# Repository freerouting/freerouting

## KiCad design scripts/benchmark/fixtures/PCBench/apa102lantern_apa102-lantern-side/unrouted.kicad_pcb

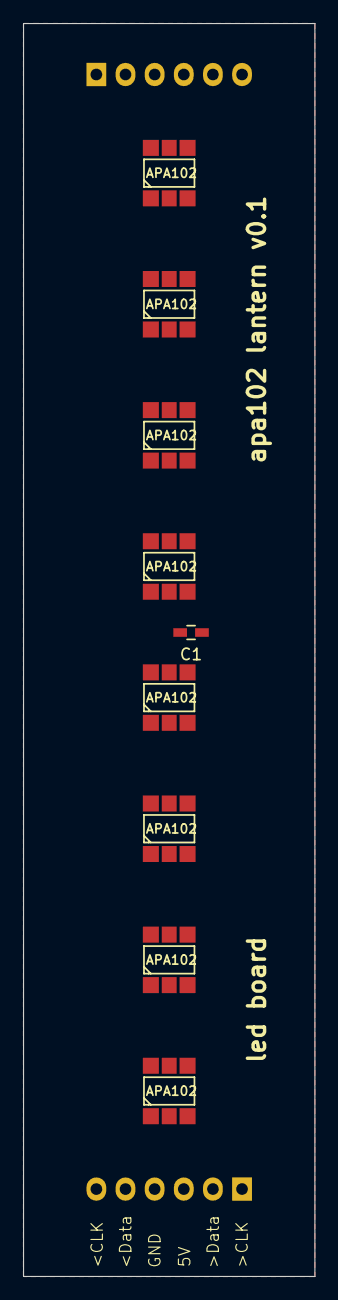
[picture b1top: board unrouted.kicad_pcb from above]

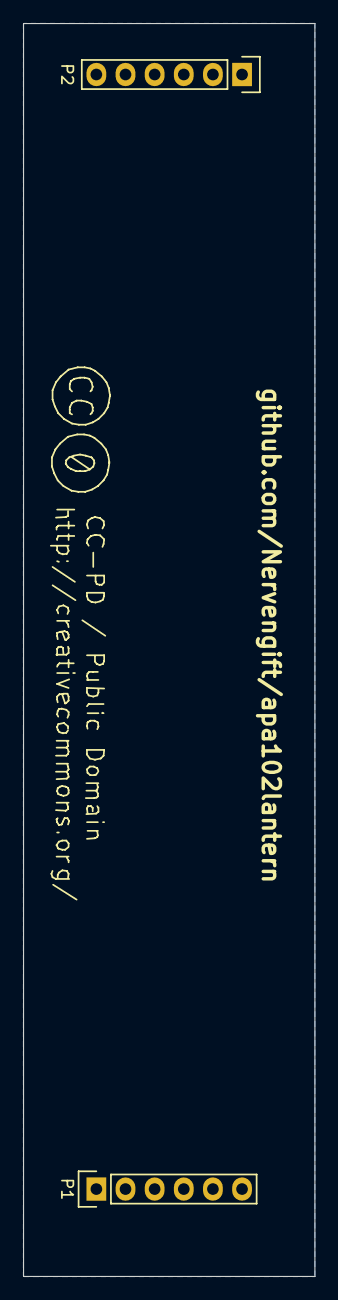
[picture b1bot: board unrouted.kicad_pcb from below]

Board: 2 copper layers, 25.4 x 109.2 mm, 11 parts (2 on the bottom side), 20 nets, no tracks yet.

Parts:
C1: 0.1u; C_0603_HandSoldering
P1, P2: CONN_01X06; Pin_Header_Straight_1x06
U1, U2, U3, U4, U5, U6, U7, U8: APA102

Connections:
/5V: C1.1, P1.3, P2.3, U1.4, U2.4, U3.4, U4.4, U5.4, U6.4, U7.4, U8.4
/>D: P1.2, U1.1
/>clk: P1.1, U1.2
/D>: P1.5, U8.6
/GND: C1.2, P1.4, P2.1, P2.2, P2.4, P2.5, P2.6, U1.3, U2.3, U3.3, U4.3, U5.3, U6.3, U7.3, U8.3
/clk>: P1.6, U8.5
unnamed: U1.5, U2.2
unnamed: U1.6, U2.1
unnamed: U2.5, U3.2
unnamed: U2.6, U3.1
unnamed: U3.5, U4.2
unnamed: U3.6, U4.1
unnamed: U4.5, U5.2
unnamed: U4.6, U5.1
unnamed: U5.5, U6.2
unnamed: U5.6, U6.1
unnamed: U6.5, U7.2
unnamed: U6.6, U7.1
unnamed: U7.5, U8.2
unnamed: U7.6, U8.1

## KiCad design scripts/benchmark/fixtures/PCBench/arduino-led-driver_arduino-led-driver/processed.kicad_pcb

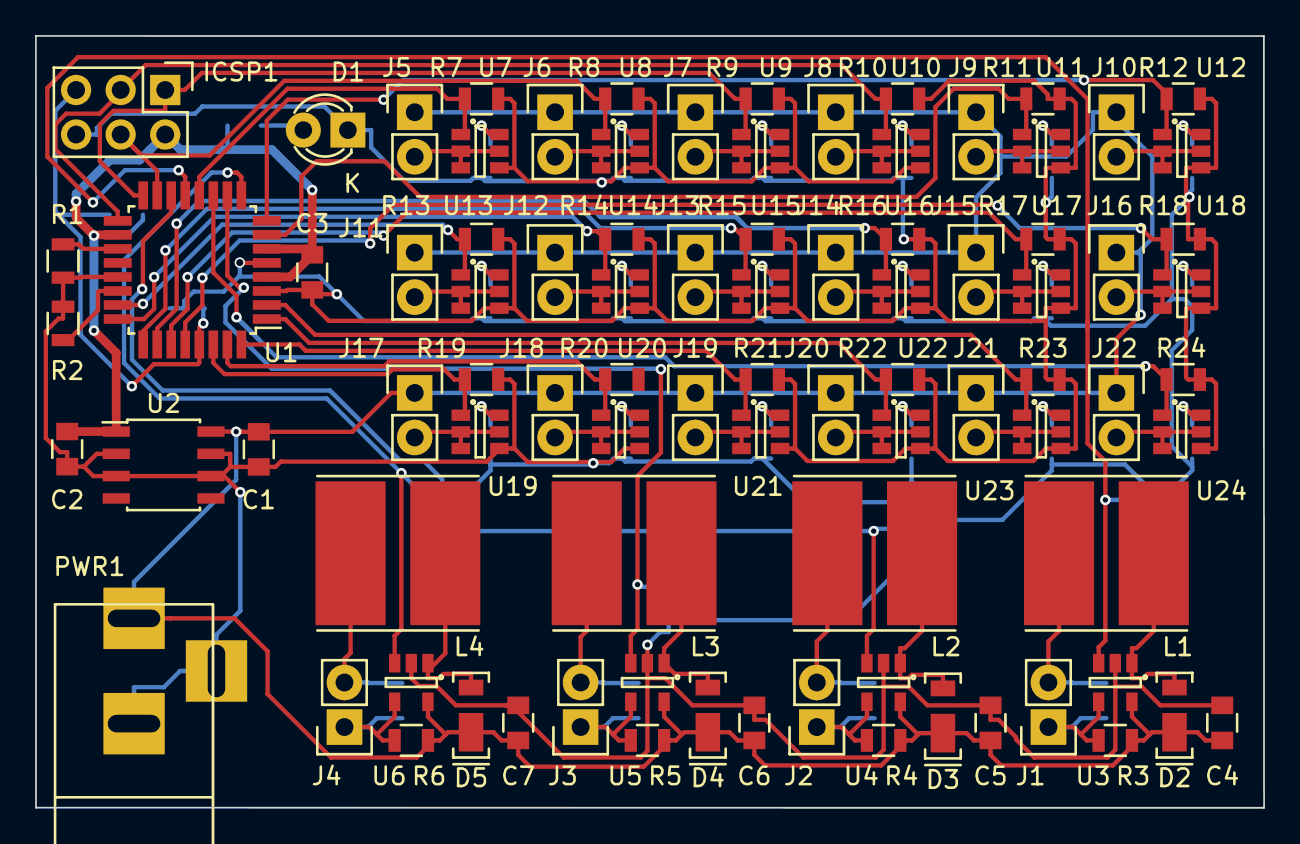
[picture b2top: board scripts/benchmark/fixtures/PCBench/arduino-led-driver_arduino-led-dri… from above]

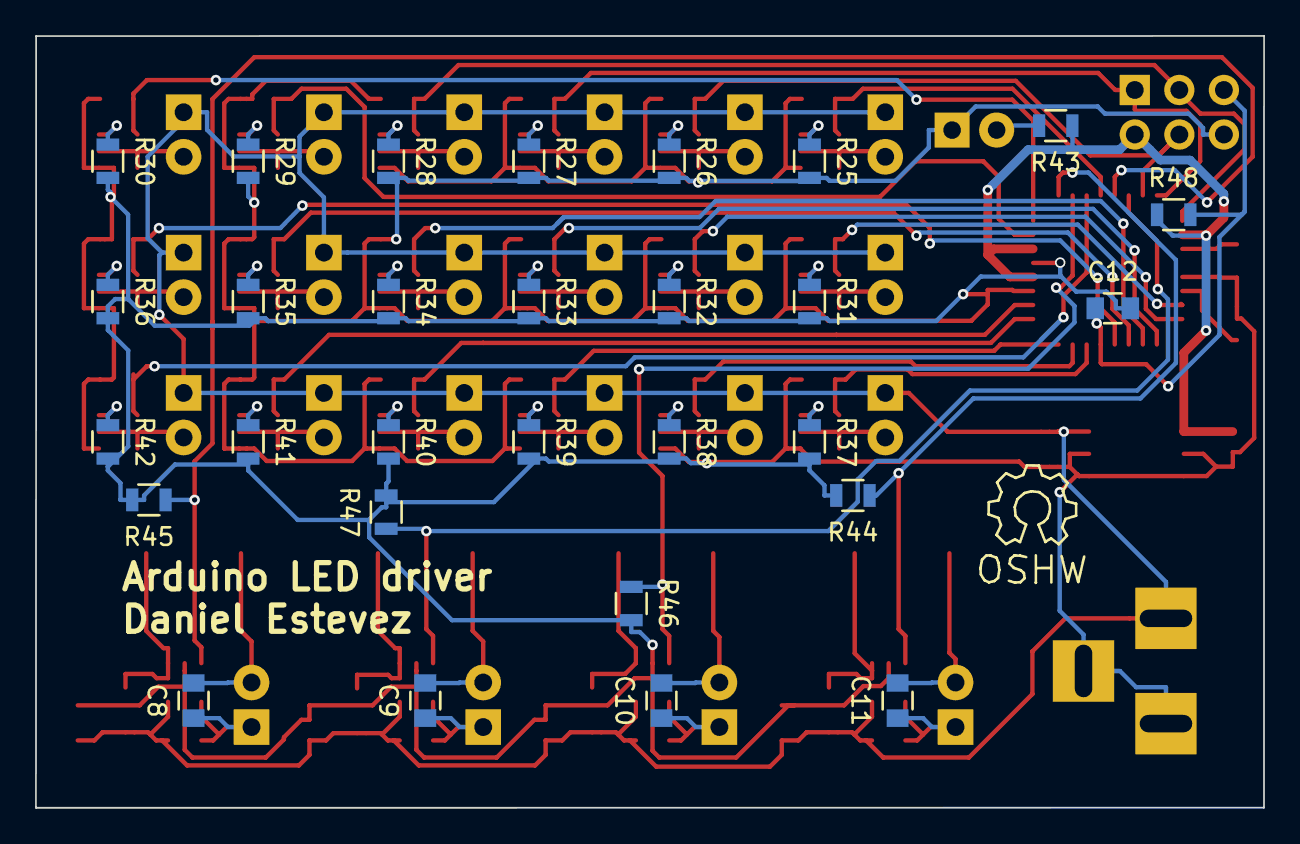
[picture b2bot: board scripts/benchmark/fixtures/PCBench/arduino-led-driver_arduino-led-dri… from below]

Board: 2 copper layers, 70.0 x 44.0 mm, 118 parts (30 on the bottom side), 77 nets.

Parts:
C1: 330n; C_0805
C2, C3, C12: 100n; C_0805
C4, C5, C6, C7: 2.2u; C_0805
C8, C9, C10, C11: 1u; C_0805
D1: LED; LED-3MM
D2, D3, D4, D5: DFLS240L; POWERDI-123
ICSP1: AVR-ISP-6; Pin_Header_Straight_2x03
J1, J2, J3, J4, J5, J6, J7, J8, J9, J10, J11, J12, J13, J14, J15, J16, J17, J18, J19, J20, J21, J22: CONN_01X02; Socket_Strip_Straight_1x02
L1, L2, L3, L4: 33u; VLP8040
Noname_1: Symbol_OSHW-Logo_SilkScreen
PWR1: BARREL_JACK
R1, R2, R7, R8, R9, R10, R11, R12, R13, R14, R15, R16, R17, R18, R19, R20, R21, R22, R23, R24, R25, R26, R27, R28, R29, R30, R31, R32, R33, R34, R35, R36, R37, R38, R39, R40, R41, R42: 100K; R_0805
R3, R4, R5, R6: 130m; R_0805
R43: 10K; R_0805
R44, R45, R46, R47: 2.2K; R_0805
R48: 10k; R_0805
U1: ATMEGA328P-A; TQFP-32_7x7mm_Pitch0.8mm
U2: L78L05ACD; SOIC-8_3.9x4.9mm_Pitch1.27mm
U3, U4, U5, U6: AL8808; SOT-23-5
U7, U8, U9, U10, U11, U12, U13, U14, U15, U16, U17, U18, U19, U20, U21, U22, U23, U24: BCR420UW6; SOT-23-6

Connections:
+5V: C2.1, C3.1, ICSP1.2, R43.1, R48.1, U1.4, U1.6, U1.18, U2.1
+12V: C1.1, C4.1, C5.1, C6.1, C7.1, D2.1, D3.1, D4.1, D5.1, J5.1, J6.1, J7.1, J8.1, J9.1, J10.1, J11.1, J12.1, J13.1, J14.1, J15.1, J16.1, J17.1, J18.1, J19.1, J20.1, J21.1, J22.1, PWR1.1, R3.2, R4.2, R5.2, R6.2, U2.8, U3.5, U4.5, U5.5, U6.5
EN1: R7.1, U1.12, U7.1
EN2: ICSP1.4, R8.1, U1.15, U8.1
EN3: ICSP1.1, R9.1, U1.16, U9.1
EN4: ICSP1.3, R10.1, U1.17, U10.1
EN5: R11.1, U1.7, U11.1
EN6: R12.1, U1.8, U12.1
EN7: R13.1, U1.23, U13.1
EN8: R14.1, U1.24, U14.1
EN9: R15.1, U1.25, U15.1
EN10: R16.1, U1.26, U16.1
EN11: R17.1, U1.27, U17.1
EN12: R18.1, U1.28, U18.1
EN13: R19.1, U1.30, U19.1
EN14: R20.1, U1.31, U20.1
EN15: R21.1, U1.32, U21.1
EN16: R22.1, U1.1, U22.1
EN17: R23.1, U1.2, U23.1
EN18: R24.1, U1.11, U24.1
GND: C1.2, C2.2, C3.2, C4.2, C5.2, C6.2, C7.2, C12.2, D1.1, ICSP1.6, PWR1.2, PWR1.3, R1.2, R2.2, R7.2, R8.2, R9.2, R10.2, R11.2, R12.2, R13.2, R14.2, R15.2, R16.2, R17.2, R18.2, R19.2, R21.2, R22.2, R23.2, R24.2, R25.2, R26.2, R27.2, R28.2, R29.2, R30.2, R31.2, R32.2, R33.2, R34.2, R35.2, R36.2, R37.2, R38.2, R39.2, R40.2, R41.2, R42.2, R44.2, R45.2, R46.2, R47.2, U1.3, U1.5, U1.21, U2.2, U2.3, U2.6, U2.7, U3.2, U4.2, U5.2, U6.2, U7.4, U8.4, U9.4, U10.4, U11.4, U12.4, U13.4, U14.4, U15.4, U16.4, U17.4, U18.4, U19.4, U20.4, U21.4, U22.4, U23.4, U24.4
unnamed: C8.1, J1.1, R3.1, U3.4
unnamed: C8.2, J1.2, L1.1
unnamed: C9.1, J2.1, R4.1, U4.4
unnamed: C9.2, J2.2, L2.1
unnamed: C10.1, J3.1, R5.1, U5.4
unnamed: C10.2, J3.2, L3.1
unnamed: C11.1, J4.1, R6.1, U6.4
unnamed: C11.2, J4.2, L4.1
unnamed: C12.1, ICSP1.5, R48.2, U1.29
unnamed: D1.2, R43.2
unnamed: D2.2, L1.2, U3.1
unnamed: D3.2, L2.2, U4.1
unnamed: D4.2, L3.2, U5.1
unnamed: D5.2, L4.2, U6.1
unnamed: J5.2, U7.2, U7.3, U7.5
unnamed: J6.2, U8.2, U8.3, U8.5
unnamed: J7.2, U9.2, U9.3, U9.5
unnamed: J8.2, U10.2, U10.3, U10.5
unnamed: J9.2, U11.2, U11.3, U11.5
unnamed: J10.2, U12.2, U12.3, U12.5
unnamed: J11.2, U13.2, U13.3, U13.5
unnamed: J12.2, U14.2, U14.3, U14.5
unnamed: J13.2, U15.2, U15.3, U15.5
unnamed: J14.2, U16.2, U16.3, U16.5
unnamed: J15.2, U17.2, U17.3, U17.5
unnamed: J16.2, U18.2, U18.3, U18.5
unnamed: J17.2, U19.2, U19.3, U19.5
unnamed: J18.2, U20.2, U20.3, U20.5
unnamed: J19.2, U21.2, U21.3, U21.5
unnamed: J20.2, U22.2, U22.3, U22.5
unnamed: J21.2, U23.2, U23.3, U23.5
unnamed: J22.2, U24.2, U24.3, U24.5
unnamed: R1.1, U1.19
unnamed: R2.1, U1.22
unnamed: R25.1, U7.6
unnamed: R26.1, U8.6
unnamed: R27.1, U9.6
unnamed: R28.1, U10.6
unnamed: R29.1, U11.6
unnamed: R30.1, U12.6
unnamed: R31.1, U13.6
unnamed: R32.1, U14.6
unnamed: R33.1, U15.6
unnamed: R34.1, U16.6
unnamed: R35.1, U17.6
unnamed: R36.1, U18.6
unnamed: R37.1, U19.6
unnamed: R38.1, U20.6
unnamed: R39.1, U21.6
unnamed: R40.1, U22.6
unnamed: R41.1, U23.6
unnamed: R42.1, U24.6
unnamed: R44.1, U1.9, U6.3
unnamed: R45.1, U1.13, U3.3
unnamed: R46.1, U1.10, U5.3
unnamed: R47.1, U1.14, U4.3

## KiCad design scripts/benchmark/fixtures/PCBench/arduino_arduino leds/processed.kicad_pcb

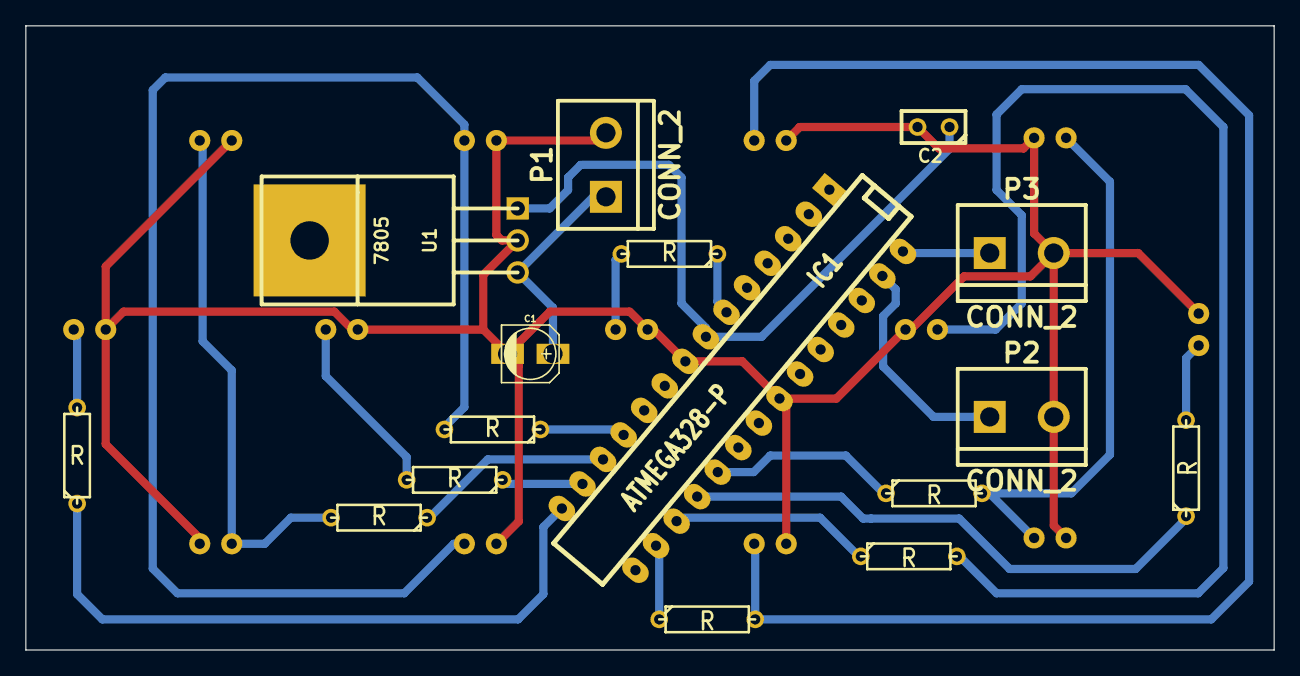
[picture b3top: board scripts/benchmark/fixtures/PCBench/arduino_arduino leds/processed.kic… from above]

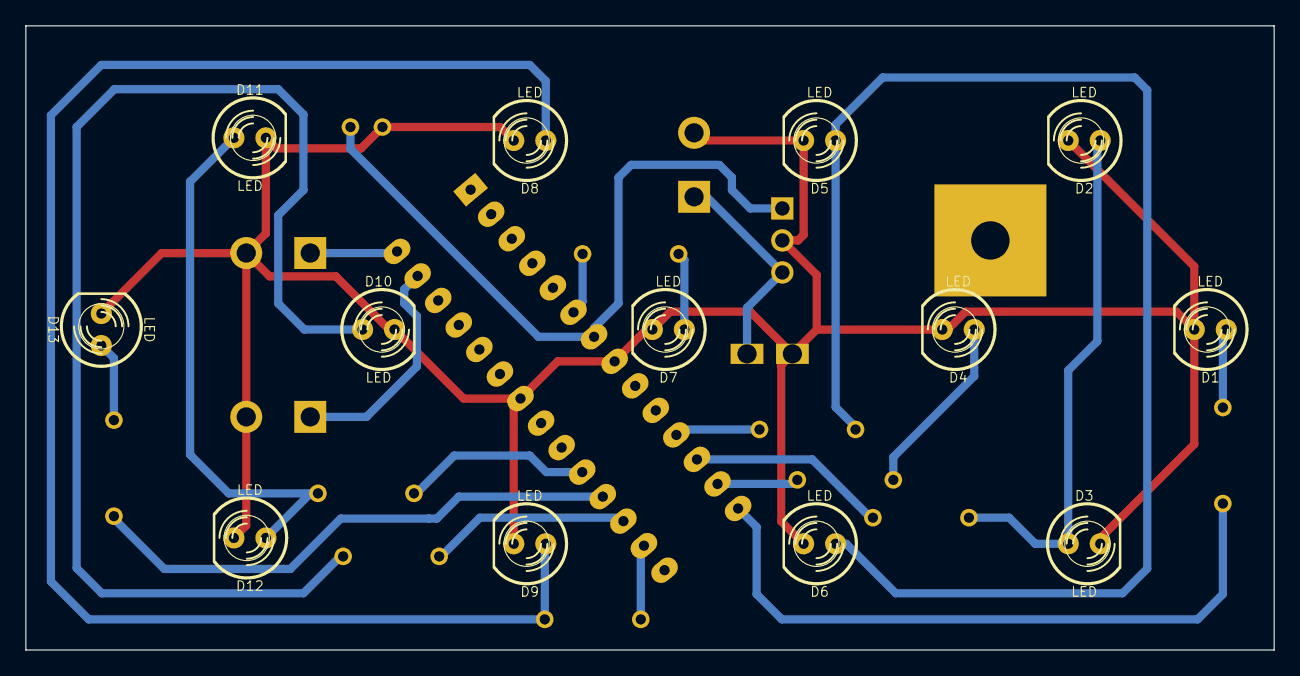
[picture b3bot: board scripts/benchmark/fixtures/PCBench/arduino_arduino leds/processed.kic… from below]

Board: 2 copper layers, 99.1 x 49.5 mm, 29 parts (13 on the bottom side), 23 nets.

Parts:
C1: CAPAPOL; c_elec_4x5.8
C2: C; C1
D1, D2, D3, D4, D5, D6, D7, D8, D9, D10, D11, D12, D13: LED; LED-5MM
IC1: ATMEGA328-P; DIP-28__300_ELL
P1, P2, P3: CONN_2; bornier2
R1, R2, R3, R4, R5, R6, R7, R8, R9: R; R3
U1: 7805; TO220

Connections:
/BTN1: IC1.27, P2.1
/BTN2: IC1.28, P3.1
/PIN4: IC1.6, R5.1
/PIN5: IC1.11, R4.1
/PIN6: IC1.12, R2.1
/PIN7: IC1.13, R3.1
/PIN8: IC1.14, R1.1
/PIN10: IC1.16, R6.1
/PIN11: IC1.17, R7.1
/PIN12: IC1.18, R9.1
/PIN13: IC1.19, R8.1
/VI: C1.1, P1.1, U1.2
/VO: C2.1, IC1.7, U1.1
GND: C1.2, C2.2, D1.2, D2.2, D3.2, D4.2, D5.2, D6.2, D7.2, D8.2, D9.2, D10.2, D11.2, D12.2, D13.2, IC1.8, IC1.22, P1.2, P2.2, P3.2, U1.3
unnamed: D7.1, R5.2
unnamed: D10.1, R7.2
unnamed: D13.1, R9.2
unnamed: D1.1, R1.2
unnamed: D4.1, R3.2
unnamed: D2.1, D3.1, R2.2
unnamed: D8.1, D9.1, R6.2
unnamed: D11.1, D12.1, R8.2
unnamed: D5.1, D6.1, R4.2

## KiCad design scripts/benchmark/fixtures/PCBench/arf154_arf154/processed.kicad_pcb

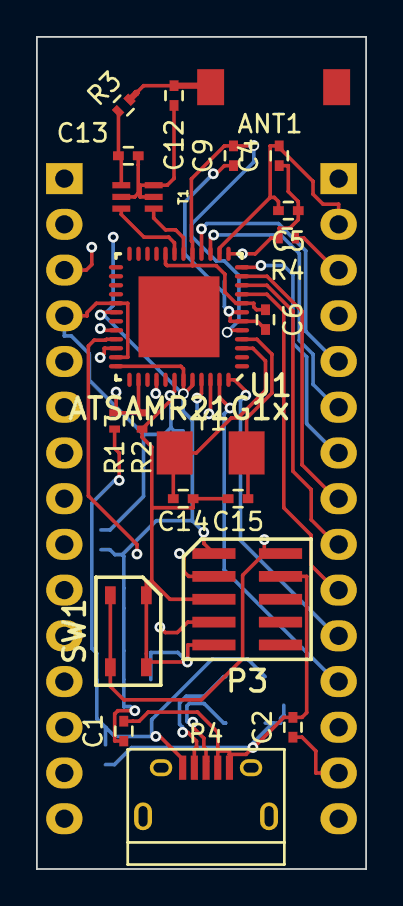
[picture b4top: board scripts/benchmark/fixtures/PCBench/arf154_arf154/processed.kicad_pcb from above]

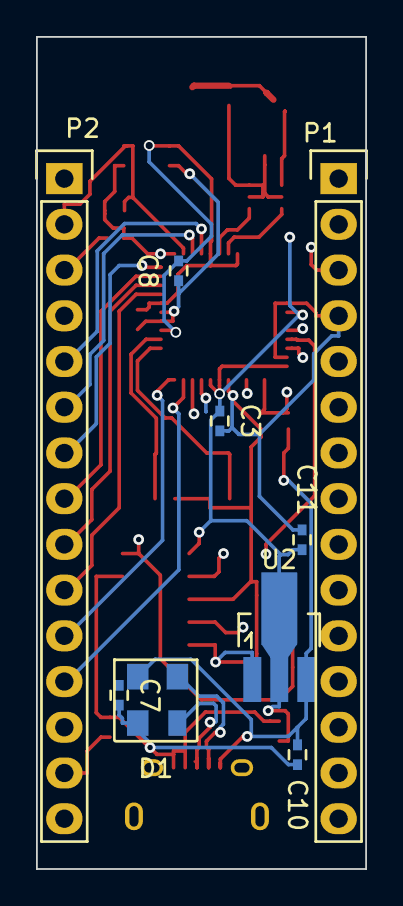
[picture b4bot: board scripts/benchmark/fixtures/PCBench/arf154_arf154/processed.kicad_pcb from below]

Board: 4 copper layers, 18.3 x 46.2 mm, 30 parts (9 on the bottom side), 26 nets.

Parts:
ANT1: antenna; CHIPANTENNA2dBi
C1: 10uF; C_0402
C2, C3, C4, C5, C6, C7, C8, C10: 100n; C_0402
C9, C11: 10u; C_0402
C12, C13: xF; C_0402
C14, C15: 18pF; C_0402
D1: PRTR5V0U2X; SOT143B
P1: Cn1; Pin_Header_Straight_1x15
P2: Cn2; Pin_Header_Straight_1x15
P3: CONN_02X05; CMxDBG
P4: USB_B; USB_Micro-B
R1, R2: 100K; R_0402
R3: xR; R_0402
R4: 10K; R_0402
SW1: SW_PUSH; tactileswitch
T1: 2450BM15A0015; JBALUN
U1: ATSAMR21G1x; QFN48EP
U2: AZ1117C; SOT89-3_Housing_Handsoldering
Y1: 16MHz; 2SMD

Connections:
/MainProcessor/BD+: T1.4, U1.18
/MainProcessor/BD-: T1.3, U1.19
/MainProcessor/PA4: P2.10, U1.9
/MainProcessor/PA5: P2.9, U1.10
/MainProcessor/PA6: P2.8, U1.11
/MainProcessor/PA7: P2.7, U1.12
/MainProcessor/PA8: P2.6, U1.15
/MainProcessor/PA9: P2.5, U1.16
/MainProcessor/PA23: R1.2, R2.1, U1.32
/MainProcessor/PB2: P2.12, U1.47
/MainProcessor/PB3: P2.11, U1.48
/MainProcessor/RST: P1.3, P2.3, P3.10, R4.1, SW1.2, U1.40
/MainProcessor/SWCLK: P3.4, U1.45
/MainProcessor/SWDIO: P3.2, U1.46
/Sheet557215E3/D+: D1.3, P4.2, U1.33
/Sheet557215E3/D-: D1.2, P4.3, U1.34
GND: C1.2, C2.2, C3.2, C4.2, C5.2, C7.2, C10.2, C11.2, C14.2, C15.2, D1.1, P1.4, P2.2, P3.3, P3.5, P3.9, P4.4, P4.5, R2.2, SW1.1, U1.14, U1.29, U1.35, U1.42, U2.1
GNDA: C6.2, C8.2, C9.2, U1.5, U1.8, U1.17, U1.20
GNDREF: C12.2, C13.2, T1.2, T1.5, T1.6
unnamed: ANT1.1, C12.1, R3.2
unnamed: C13.1, R3.1, T1.1
unnamed: C14.1, U1.3, Y1.1
unnamed: C15.1, U1.4, Y1.2
VAA: C6.1, C8.1, C9.1, U1.6, U1.7
VCC: C10.1, D1.4, P4.1, R1.1, U2.3
VDD: C1.1, C2.1, C3.1, C4.1, C5.1, C11.1, P2.14, P3.1, R4.2, U1.13, U1.30, U1.36, U1.43, U1.44, U2.2
